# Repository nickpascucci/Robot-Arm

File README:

Robot Arm GitHub Repository

This repository contains the content I've created in developing a
robot arm. The arm is built entirely from scratch, with the exception
of an Arduino for control and some servos for movement. All of the
parts are given in QCAD .dxf format, and are machinable on a standard
lathe/mill setup. The project is mothballed for the time being, but
maybe some of the info here will be of use.

Licenses:
Software: MIT License. 

Drawings/Images: Creative Commons Attribution-ShareAlike.

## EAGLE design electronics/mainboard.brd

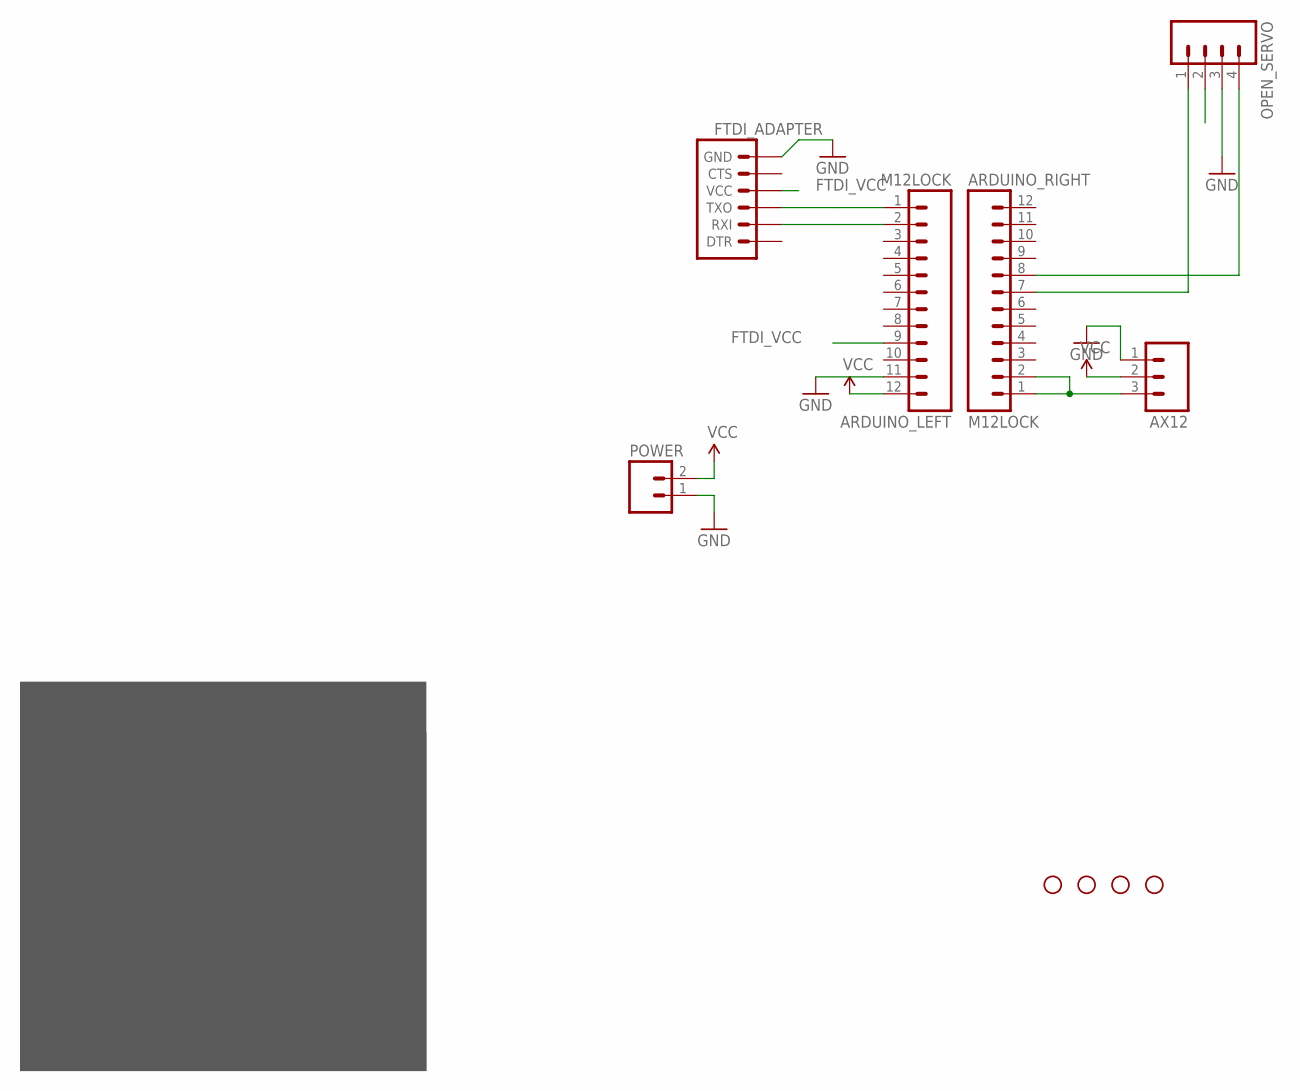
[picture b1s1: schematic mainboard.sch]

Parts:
ARDUINO_LEFT: M12LOCK; 1X12_LOCK
ARDUINO_RIGHT: M12LOCK; 1X12_LOCK
AX12: M03LOCK; 1X03_LOCK
FTDI_ADAPTER: ARDUINO_SERIAL_PROGRAMLOCK; 1X06_LOCK
JP1, JP2, JP3, JP4: STAND-OFF
OPEN_SERVO: M04LOCK; 1X04_LOCK
POWER: M023.5MM; SCREWTERMINAL-3.5MM-2

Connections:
AX_DATA: ARDUINO_RIGHT.1, ARDUINO_RIGHT.2, AX12.3
FTDI_RX: ARDUINO_LEFT.2, FTDI_ADAPTER.2 (RXI)
FTDI_TX: ARDUINO_LEFT.1, FTDI_ADAPTER.3 (TXO)
FTDI_VCC: ARDUINO_LEFT.9, FTDI_ADAPTER.4 (VCC)
GND: ARDUINO_LEFT.11, AX12.1, FTDI_ADAPTER.6 (GND), OPEN_SERVO.3, POWER.1
unnamed: ARDUINO_RIGHT.7, OPEN_SERVO.1
unnamed: ARDUINO_RIGHT.8, OPEN_SERVO.4
VCC: ARDUINO_LEFT.12, AX12.2, POWER.2

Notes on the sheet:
8 Pin Header, Pol
Parts List
Part Name
Component
ATX_ADAPTER
AX12
V_REG_317
74HC4052
FTDI_ADAPTER
ARDUINO_LEFT
ARDUINO_RIGHT
12 Pin Header, Fem
3 Pin Header
6 Pin Header, Pol
LM317 Adj Volt Reg
74HC4052 Serial Mux
OPEN_SERVO
4 Pin Header, Pol
MBT2222ALT3G NPN
Q1, Q2
OPTOISOLATOR
ILD213T
All Resistors
0805 Surface Mount

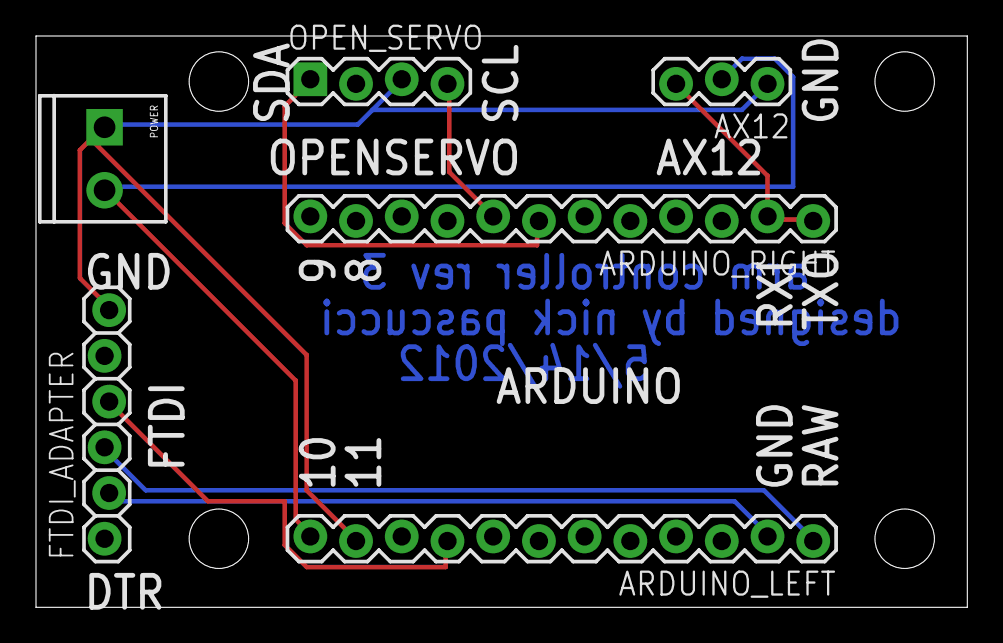
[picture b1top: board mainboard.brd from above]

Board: 2 copper layers, 51.7 x 31.7 mm, 10 parts (0 on the bottom side), 8 nets.

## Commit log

2011-04-27 Added testing firmware.
2011-04-27 Added readme and licenses.
2011-04-27 Shortened CC license.
2011-04-27 Added desktop software.
2011-05-08 Added multiplexer library.
2011-05-08 Added serial command support.
2011-05-09 Added serial command support to replace various helper functions.
2011-05-11 Commit before merge.
2011-05-11 Added code for testing connection and selecting port.
2011-05-11 Added finalization method.
2011-05-11 Removed compiled bytecode files.
2011-05-11 Fixed module names in InverseKinematics.
2011-05-11 Added .quickly file
2011-05-15 Fixed various bugs.
    The ground on the LED side of the optoisolator was incorrectly wired
    to FTDI ground for both pins; this was rectified.
    The board was resized to provide more room for wiring and easier
    soldering. I also added another mounting hole.
    Various changes made to software, such as the beginnings of a test
    routine in the firmware and adding GUI support for such.
2011-07-25 Added code to read in a robot descriptor file and parse it. Still needs some work.
2012-05-15 Reduced main board complexity significantly.
2014-06-24 Clean up repository a bit
2014-06-24 Update README and add experiments folder.
